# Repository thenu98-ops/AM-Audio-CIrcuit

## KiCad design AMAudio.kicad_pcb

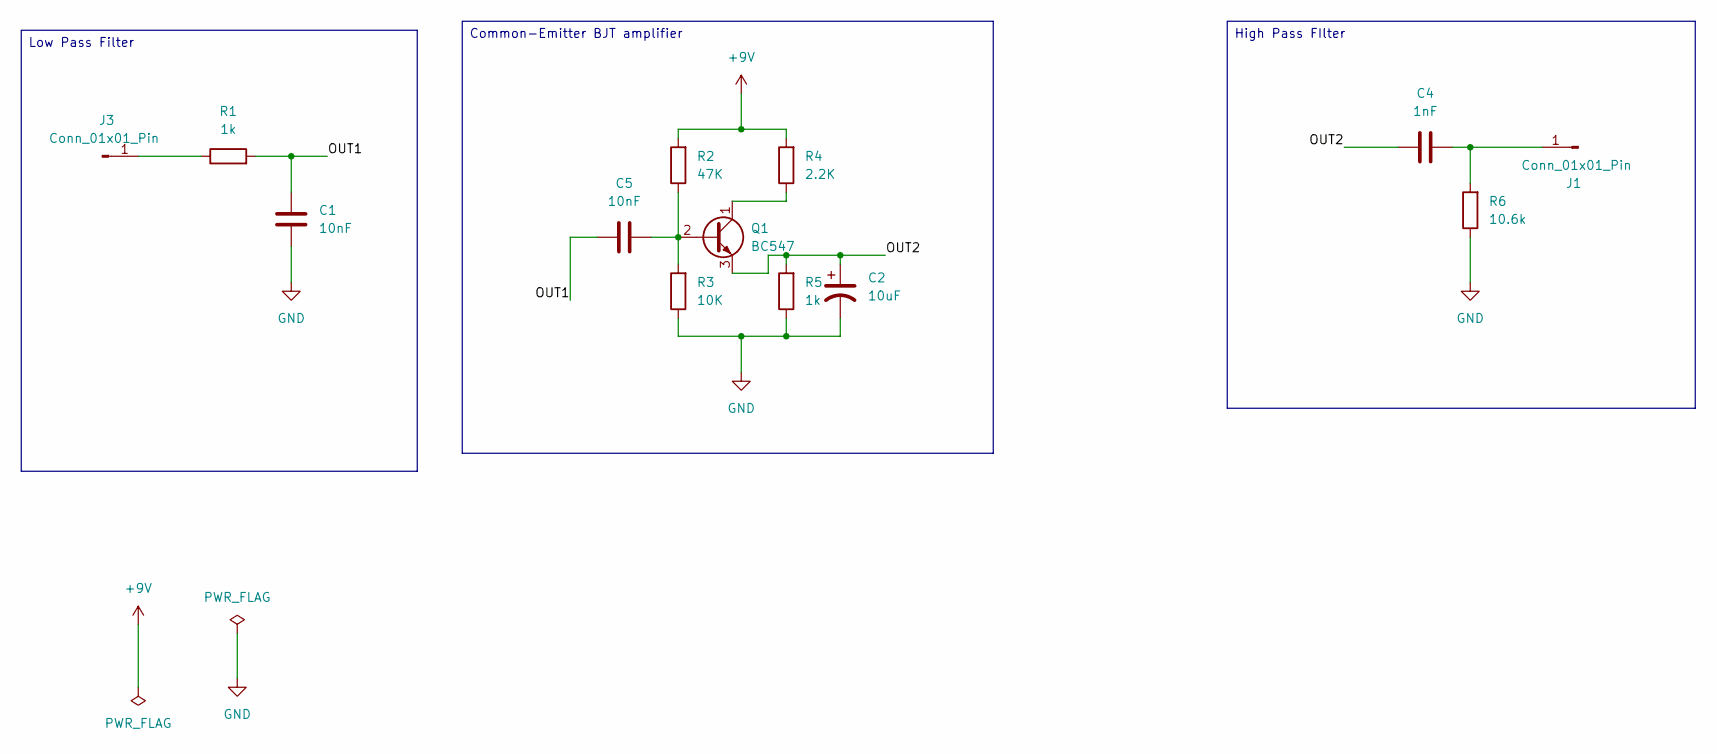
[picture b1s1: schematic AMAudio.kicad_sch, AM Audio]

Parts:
C1, C5: 10nF; C_0805_2012Metric_Pad1.18x1.45mm_HandSolder
C2: 10uF; CP_Elec_4x5.4
C4: 1nF; C_0805_2012Metric_Pad1.18x1.45mm_HandSolder
J1, J3: Conn_01x01_Pin; PinSocket_1x01_P2.54mm_Vertical
Q1: BC547; TO-92_Inline
R1, R5: 1k; R_0805_2012Metric_Pad1.20x1.40mm_HandSolder
R2: 47K; R_0805_2012Metric_Pad1.20x1.40mm_HandSolder
R3: 10K; R_0805_2012Metric_Pad1.20x1.40mm_HandSolder
R4: 2.2K; R_0805_2012Metric_Pad1.20x1.40mm_HandSolder
R6: 10.6k; R_0805_2012Metric_Pad1.20x1.40mm_HandSolder

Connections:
+9V: R2.2, R4.2
/OUT1: C1.1, C5.1, R1.2
/OUT2: C2.1, C4.1, Q1.3 (E), R5.2
GND: C1.2, C2.2, R3.1, R5.1, R6.1
unnamed: C4.2, J1.1, R6.2
unnamed: J3.1, R1.1
unnamed: C5.2, Q1.2 (B), R2.1, R3.2
unnamed: Q1.1 (C), R4.1

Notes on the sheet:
Low Pass Filter
Common-Emitter BJT amplifier
High Pass FIlter

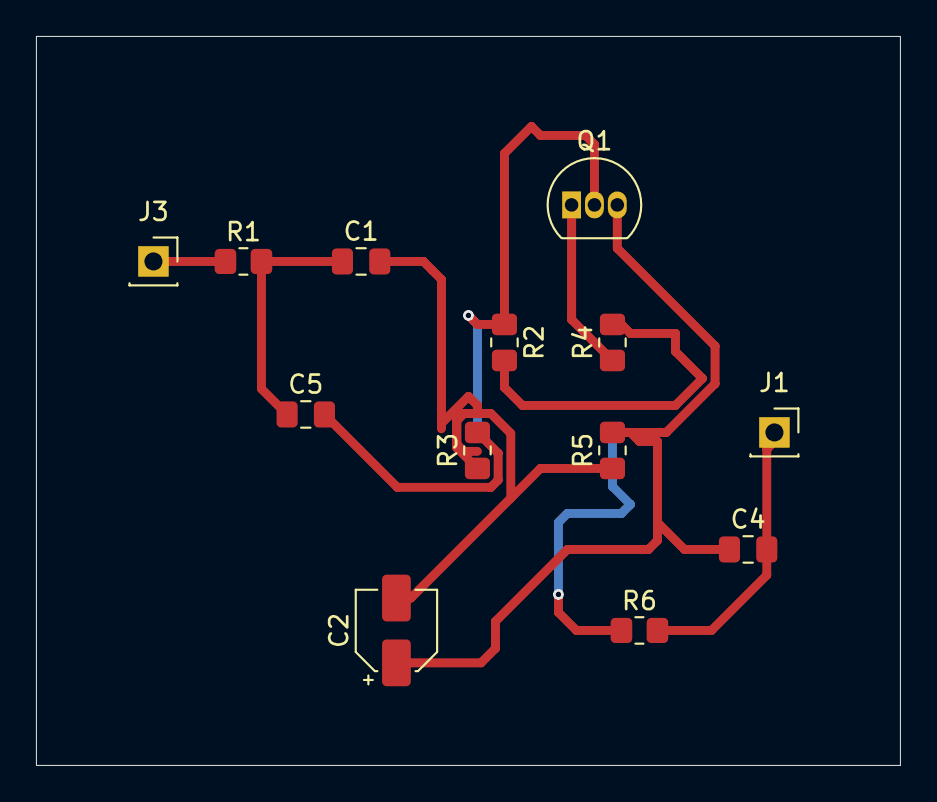
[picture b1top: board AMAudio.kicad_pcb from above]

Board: 2 copper layers, 48.0 x 40.5 mm, 13 parts (0 on the bottom side), 8 nets.
